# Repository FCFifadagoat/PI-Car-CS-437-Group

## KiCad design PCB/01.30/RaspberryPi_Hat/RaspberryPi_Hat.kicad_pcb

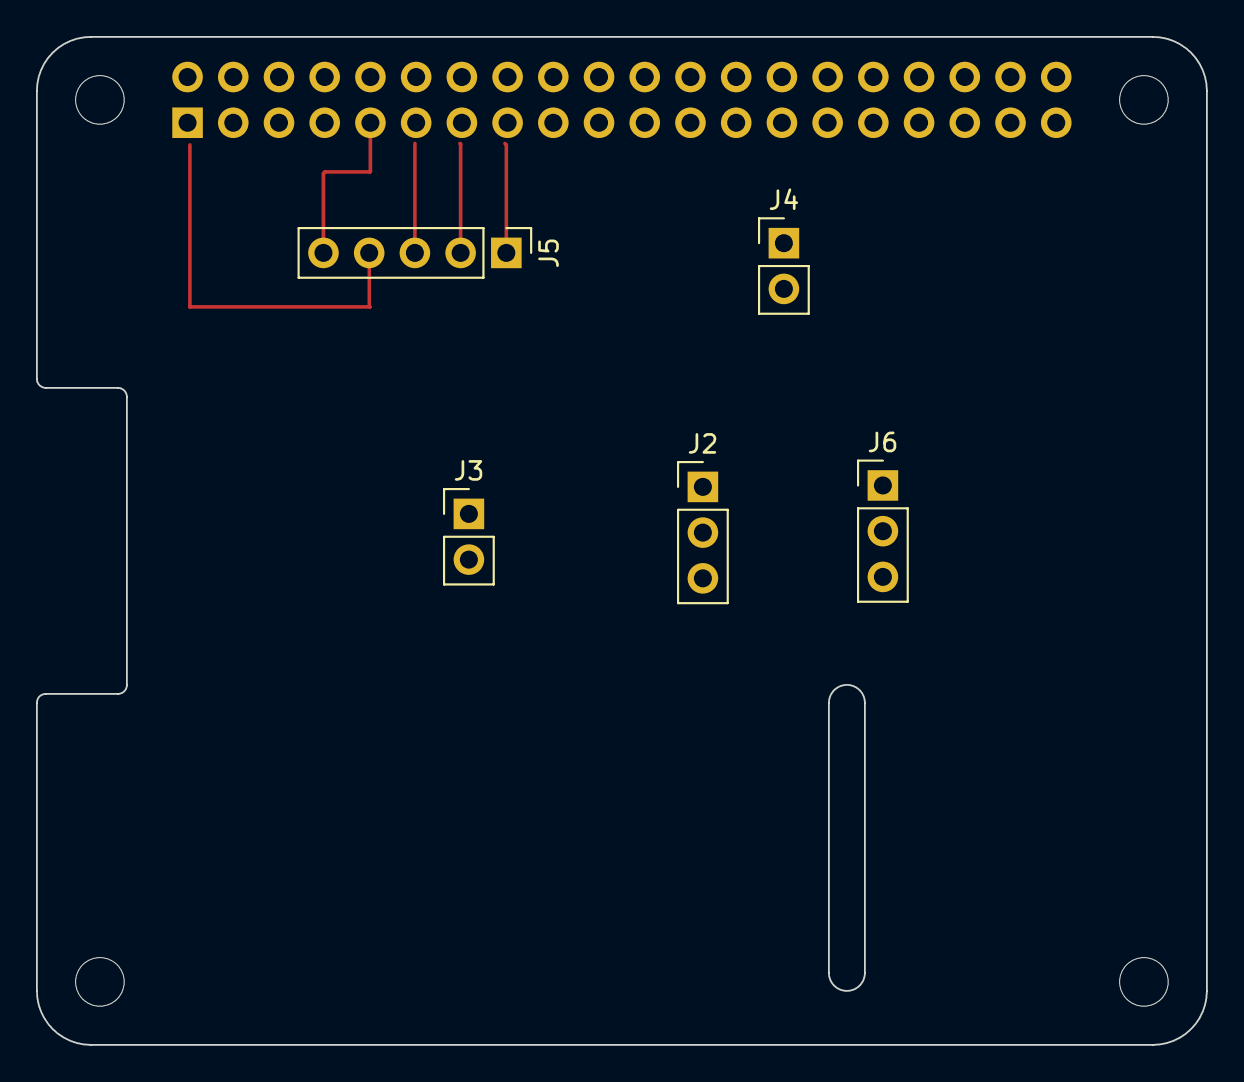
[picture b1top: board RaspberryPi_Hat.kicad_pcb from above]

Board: 2 copper layers, 65.0 x 56.0 mm, 10 parts (1 on the bottom side), 4 nets.

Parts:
J1: GPIO; PinSocket_2x20_P2.54mm_Vertical
J2, J6: Conn_01x03; PinHeader_1x03_P2.54mm_Vertical
J3, J4: Conn_01x02; PinHeader_1x02_P2.54mm_Vertical
J5: Conn_01x05; PinHeader_1x05_P2.54mm_Vertical
MH1, MH2, MH3, MH4: MountingHole_2.7mm_M2.5

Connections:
+3V3: J1.1, J1.17, J5.4, J6.1
+5V: J1.2, J1.4
/GPIO5: J1.29, J6.3
GND: J1.6, J1.9, J1.14, J1.20, J1.25, J1.30, J1.34, J1.39, J2.2, J5.5, J6.2

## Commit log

2026-01-29 added mapping file
2026-01-29 Create Begin
2026-01-29 added test file
2026-01-29 Created PCB folder
2026-01-29 Add files via upload
    Added PCB project files
2026-01-29 Added code to mapping.py
2026-01-30 Photo interruptor added
2026-01-31 added alternate mapping file
2026-02-01 Finished PCB implementation
2026-02-02 implemented way to have car avoid obstacle and continue
2026-02-02 Basic Naive mapping added
2026-02-02 Adds driving.py
2026-02-03 Added left/right scanning before committing to a turn & simplified logic
2026-02-04 Create driving_test
    Test shorter danger distance and commit to turn differently
2026-02-04 Turn servo back straight when LeftDistance >= RightDistance
2026-02-04 Added driving2.py for testing
2026-02-06 added minor tweak to pcb
2026-02-10 PCB Layout updated
2026-02-10 100x100 grid and obstacle/free-space interpolation logic
2026-02-12 Step6 Done
2026-02-12 minor issue fixed
2026-02-12 indentation error fixed
    Added obstacle mapping to grid based on angle and distance.
2026-02-18 Add code for step6 with mounted ultrasonic sensor
2026-02-19 Added detect_stop_sign.py
2026-02-19 step6_render_mounted
    Added a render attempt of the OpenCV grid
2026-02-19 groundwork for combined car setup
2026-02-19 added cooldown for stop sign scanner and reset camera for stop sign scan
2026-02-20 added A* algo
2026-02-20 Added hybrid_astar_obstacle_navigation.py
2026-02-21 Improves pathfinding
2026-02-21 Added full_self_driving.py
2026-02-21 Updates stop sign waiting time
2026-03-18 Lab 2
2026-03-19 Added bluetooth functionality
2026-03-21 Add batt to viewer
    UI has batt percentage taken from Pi - just see index.html and pi_server.py
2026-03-22 Complete repository cleanup and organization
2026-03-22 test
2026-04-26 Part 1, Lab 5 using Jupyter NB
    Test
2026-05-09 Started basis for water, food dispensing and frontend
2026-05-09 Added food dispensing mechanism and added notifications for dashboard
2026-05-09 Useful comment for hx711
2026-05-11 Add cat detection with examples
2026-05-12 Rename folder
    Final project
2026-05-12 Alt Detection Stuff
2026-05-13 added live sensing and data gathering
2026-05-13 Cleaned up
2026-05-13 Added live feed
2026-05-13 made csv2 mandatory
2026-05-13 added back csv2 optional
